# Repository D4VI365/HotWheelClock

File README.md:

# HotWheels Clock
A wall clock that uses two hotwheels to idicate the time, the cars will be moved by two magnets behind the main board of the clock moved by two geared wheels with motors, all powered froma a 10000mAh battery and controlled by an esp32 in order to calibrate the time automatically via internet.

Wiring Schematic:

PCB:

CAD model: 

Print list:
1xCenterSupport
1xInnerCurb1
12xInnerCurb2
1xInnerGear
3xInnerHook
1xInnerHookHall
1xInnerMotorMount
3xMidSupport1
4xMidSupport2
1xMidSupport3
2xMotorGear
2xOuterCurb1
2xOuterCurb2
18xOuterCurb3
4xOuterGear
2xOuterHook
1xOuterHook2
1xOuterHookHall
1xOuterMotorMount
1xTyre
1xWheelRim

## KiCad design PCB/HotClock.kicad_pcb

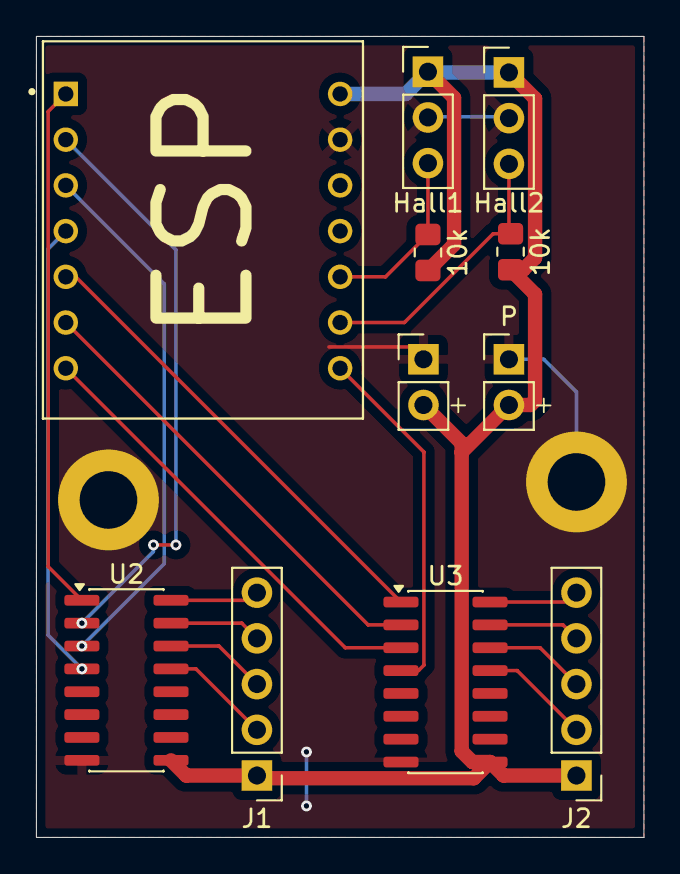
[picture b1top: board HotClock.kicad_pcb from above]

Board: 2 copper layers, 33.8 x 44.5 mm, 13 parts (0 on the bottom side), 20 nets.

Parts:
10k, 10k#2: 10k; R_0805_2012Metric_Pad1.20x1.40mm_HandSolder
C1: 470/100uf; PinHeader_1x02_P2.54mm_Vertical
H1, H2: MountingHole_Pad; MountingHole_3.2mm_M3_DIN965_Pad
Hall1: HallSensor2; PinHeader_1x03_P2.54mm_Vertical
Hall2: HallSensor1; PinHeader_1x03_P2.54mm_Vertical
J1: MotorHours; PinHeader_1x05_P2.54mm_Vertical
J2: MotorMinutes; PinHeader_1x05_P2.54mm_Vertical
P: Alimentation; PinHeader_1x02_P2.54mm_Vertical
U1: XIAO_ESP32C3; MODULE_XIAO_ESP32C3
U2, U3: ULN2003A; SOIC-16_3.9x9.9mm_P1.27mm

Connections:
5V: 10k.2, 10k#2.2, C1.2, Hall1.1, Hall2.1, J1.1, J2.1, P.2, U1.14 (VUSB), U2.9 (COM), U3.9 (COM)
/GND: C1.1, H1.1, H2.1, Hall1.2, Hall2.2, P.1, U1.13 (GND), U2.8 (GND), U3.8 (GND)
/P1: U1.1 (D0), U2.1 (I1)
/P2: U1.2 (D1), U2.2 (I2)
/P3: U1.3 (D2), U2.3 (I3)
/P4: U1.4 (D3), U2.4 (I4)
/P5: U1.5 (D4), U3.1 (I1)
/P6: U1.6 (D5), U3.2 (I2)
/P7: U1.7 (TX_D6), U3.3 (I3)
/P8: U1.8 (RX_D7), U3.4 (I4)
/P9: 10k#2.1, Hall2.3, U1.9 (D8)
/P10: 10k.1, Hall1.3, U1.10 (D9)
unnamed: J1.2, U2.13 (O4)
unnamed: J1.3, U2.14 (O3)
unnamed: J1.4, U2.15 (O2)
unnamed: J1.5, U2.16 (O1)
unnamed: J2.2, U3.13 (O4)
unnamed: J2.3, U3.14 (O3)
unnamed: J2.4, U3.15 (O2)
unnamed: J2.5, U3.16 (O1)

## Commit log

2026-04-08 Upload File
2026-04-13 Add PCB Gerber files (Gerber.zip)
    Add PCB/Gerber.zip containing PCB manufacturing (Gerber) files. This binary archive provides the fabrication data for the board and is added to the PCB/ directory for production and review.
